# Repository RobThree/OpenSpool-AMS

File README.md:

# OpenSpool AMS

This repository contains the PCB design for the [OpenSpool](https://github.com/spuder/OpenSpool) project. This PCB can connect up to 5 PN532 NFC reader modules to an ESP32 S3 WROOM devkit board.

## How to use

You can use this board on top, or on the bottom of your ESP32. Depending on which side you solder the female (or male) sockets (or pinheaders) you can then use the other side to connect your NFC readers to. The pins are in the same order as the pins on the PN532 board so you should be able to use dupont wires 6-wide (without tearing the wires apart). The wires should then go straight from this board to the PN532 module.

Note that the 'connectorblock' has an extra row of pins for 5 volts. You don't **need** to populate this. However, if for some reason your PN532 readers won't work you can try connecting the 3V3 wire to this 5V rail. Some PN532 reader modules apparently won't work on 3V3 (I haven't encountered them yet).

## What you need

* `1x` ESP32 S3 WROOM DEVKIT
* `2x` 22 pin female pin socket or pin header
* `6x` 5 pin female pin socket or pin header (`+1` if you want to populate the 5V one whilst also populating the 3V3 one)
* `1x per PN532 reader` 6 pin wide dupont wire male/female as you see fit

## Steps

1. Determine which side of the board you want to go on top or on the bottom of the ESP32. This is the side you solder the 22 pin female socket or pinheader to.
2. Solder the 6 (or 7) female sockets or pinheaders to the other side of this PCB so the wires won't have to be routed between the ESP32 and this board.
3. Connect the ESP32 to this board, hook up the PN532 modules to this board. Pay attention that you connect each board to a numbered column (`0` through `4`) and pay extra close attention the the 3V3 and 5V pins to ensure the correct ones go to VCC on the PN532 module.

For more instructions, or how to proceed after this, see the [OpenSpool project](https://github.com/spuder/OpenSpool).

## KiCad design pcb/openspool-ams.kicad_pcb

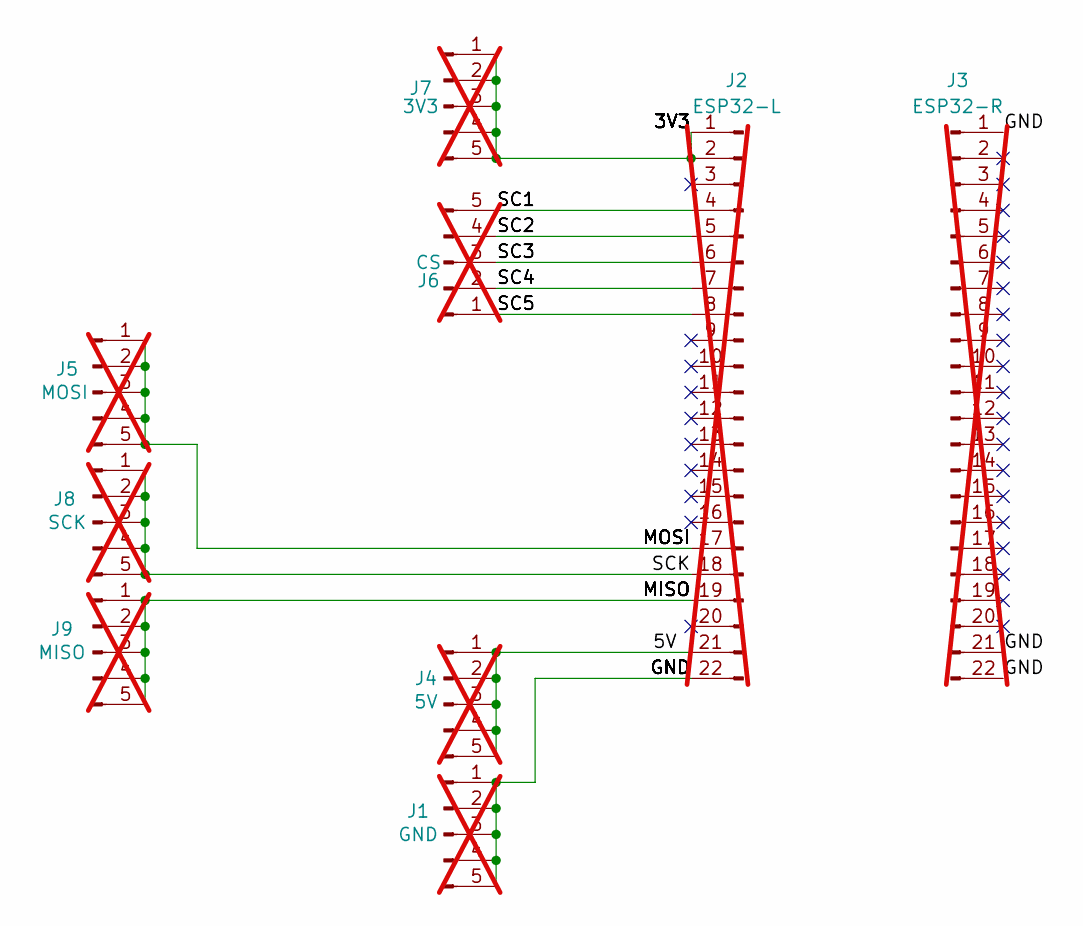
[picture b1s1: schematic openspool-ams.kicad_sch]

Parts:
J1: GND; PinSocket_1x05_P2.54mm_Vertical; not fitted
J2: ESP32-L; PinSocket_1x22_P2.54mm_Vertical; not fitted
J3: ESP32-R; PinSocket_1x22_P2.54mm_Vertical; not fitted
J4: 5V; PinSocket_1x05_P2.54mm_Vertical; not fitted
J5: MOSI; PinSocket_1x05_P2.54mm_Vertical; not fitted
J6: CS; PinSocket_1x05_P2.54mm_Vertical; not fitted
J7: 3V3; PinSocket_1x05_P2.54mm_Vertical; not fitted
J8: SCK; PinSocket_1x05_P2.54mm_Vertical; not fitted
J9: MISO; PinSocket_1x05_P2.54mm_Vertical; not fitted

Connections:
/3V3: J2.1 (3V3_A), J2.2 (3V3_B), J7.1, J7.2, J7.3, J7.4, J7.5
/5V: J2.21 (5V), J4.1, J4.2, J4.3, J4.4, J4.5
/GND: J1.1, J1.2, J1.3, J1.4, J1.5, J2.22 (GND), J3.1 (GND_A), J3.21 (GND_B), J3.22 (GND_C)
/MISO: J2.19 (13), J9.1, J9.2, J9.3, J9.4, J9.5
/MOSI: J2.17 (11), J5.1, J5.2, J5.3, J5.4, J5.5
/SC1: J2.4, J6.5
/SC2: J2.5, J6.4
/SC3: J2.6, J6.3
/SC4: J2.7, J6.2
/SC5: J2.8 (15), J6.1
/SCK: J2.18 (12), J8.1, J8.2, J8.3, J8.4, J8.5

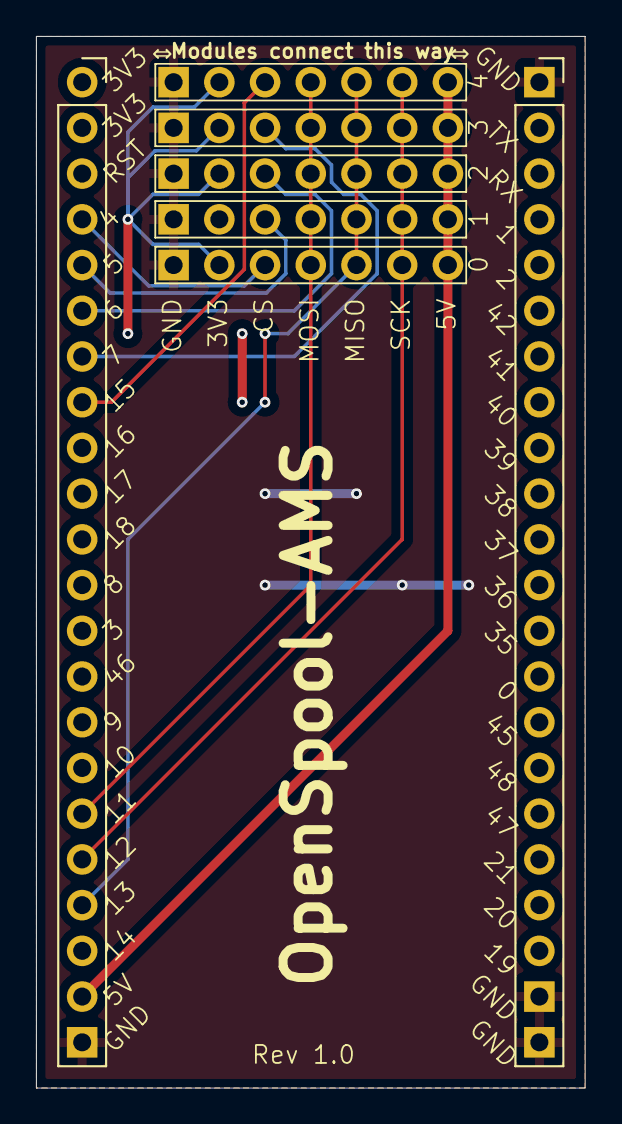
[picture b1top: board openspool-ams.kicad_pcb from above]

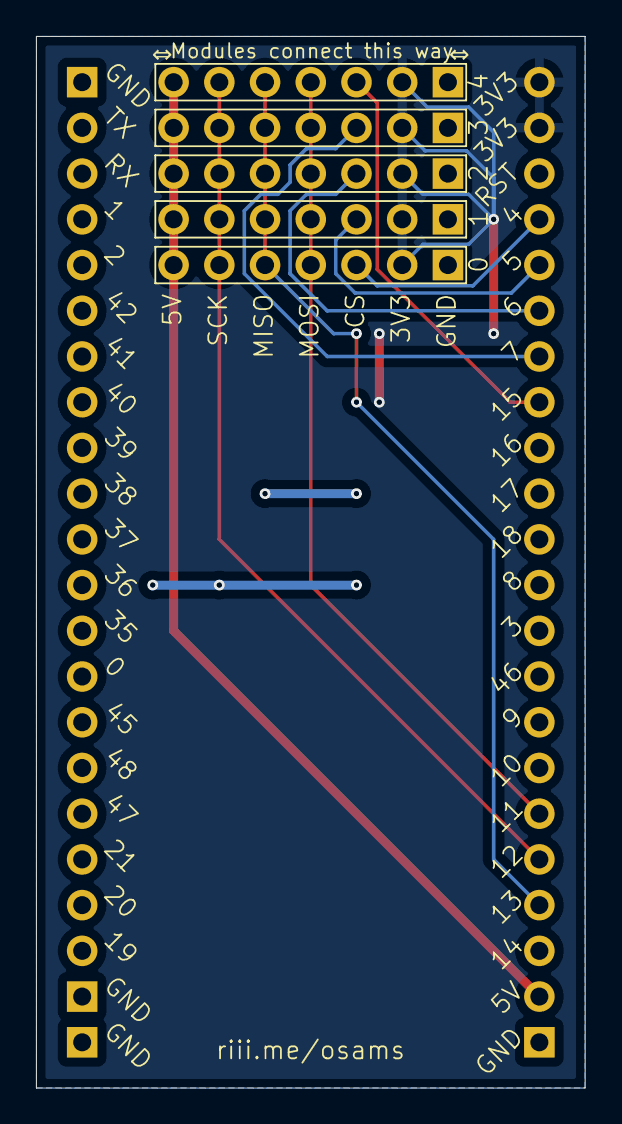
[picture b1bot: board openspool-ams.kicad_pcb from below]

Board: 2 copper layers, 30.5 x 58.4 mm, 9 parts (7 on the bottom side), 11 nets.

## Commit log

2025-04-02 Add LICENSE and README
2025-04-02 Improved silkscreen. Added preview images.
2025-04-02 Added hints to silkscreen
2025-04-02 Typo
